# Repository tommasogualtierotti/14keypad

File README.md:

# 14keypad
14 keys programmable Macropad, based on RP2040 MCU from Raspberry Pi, running [KMK](https://github.com/KMKfw/kmk_firmware) firmware

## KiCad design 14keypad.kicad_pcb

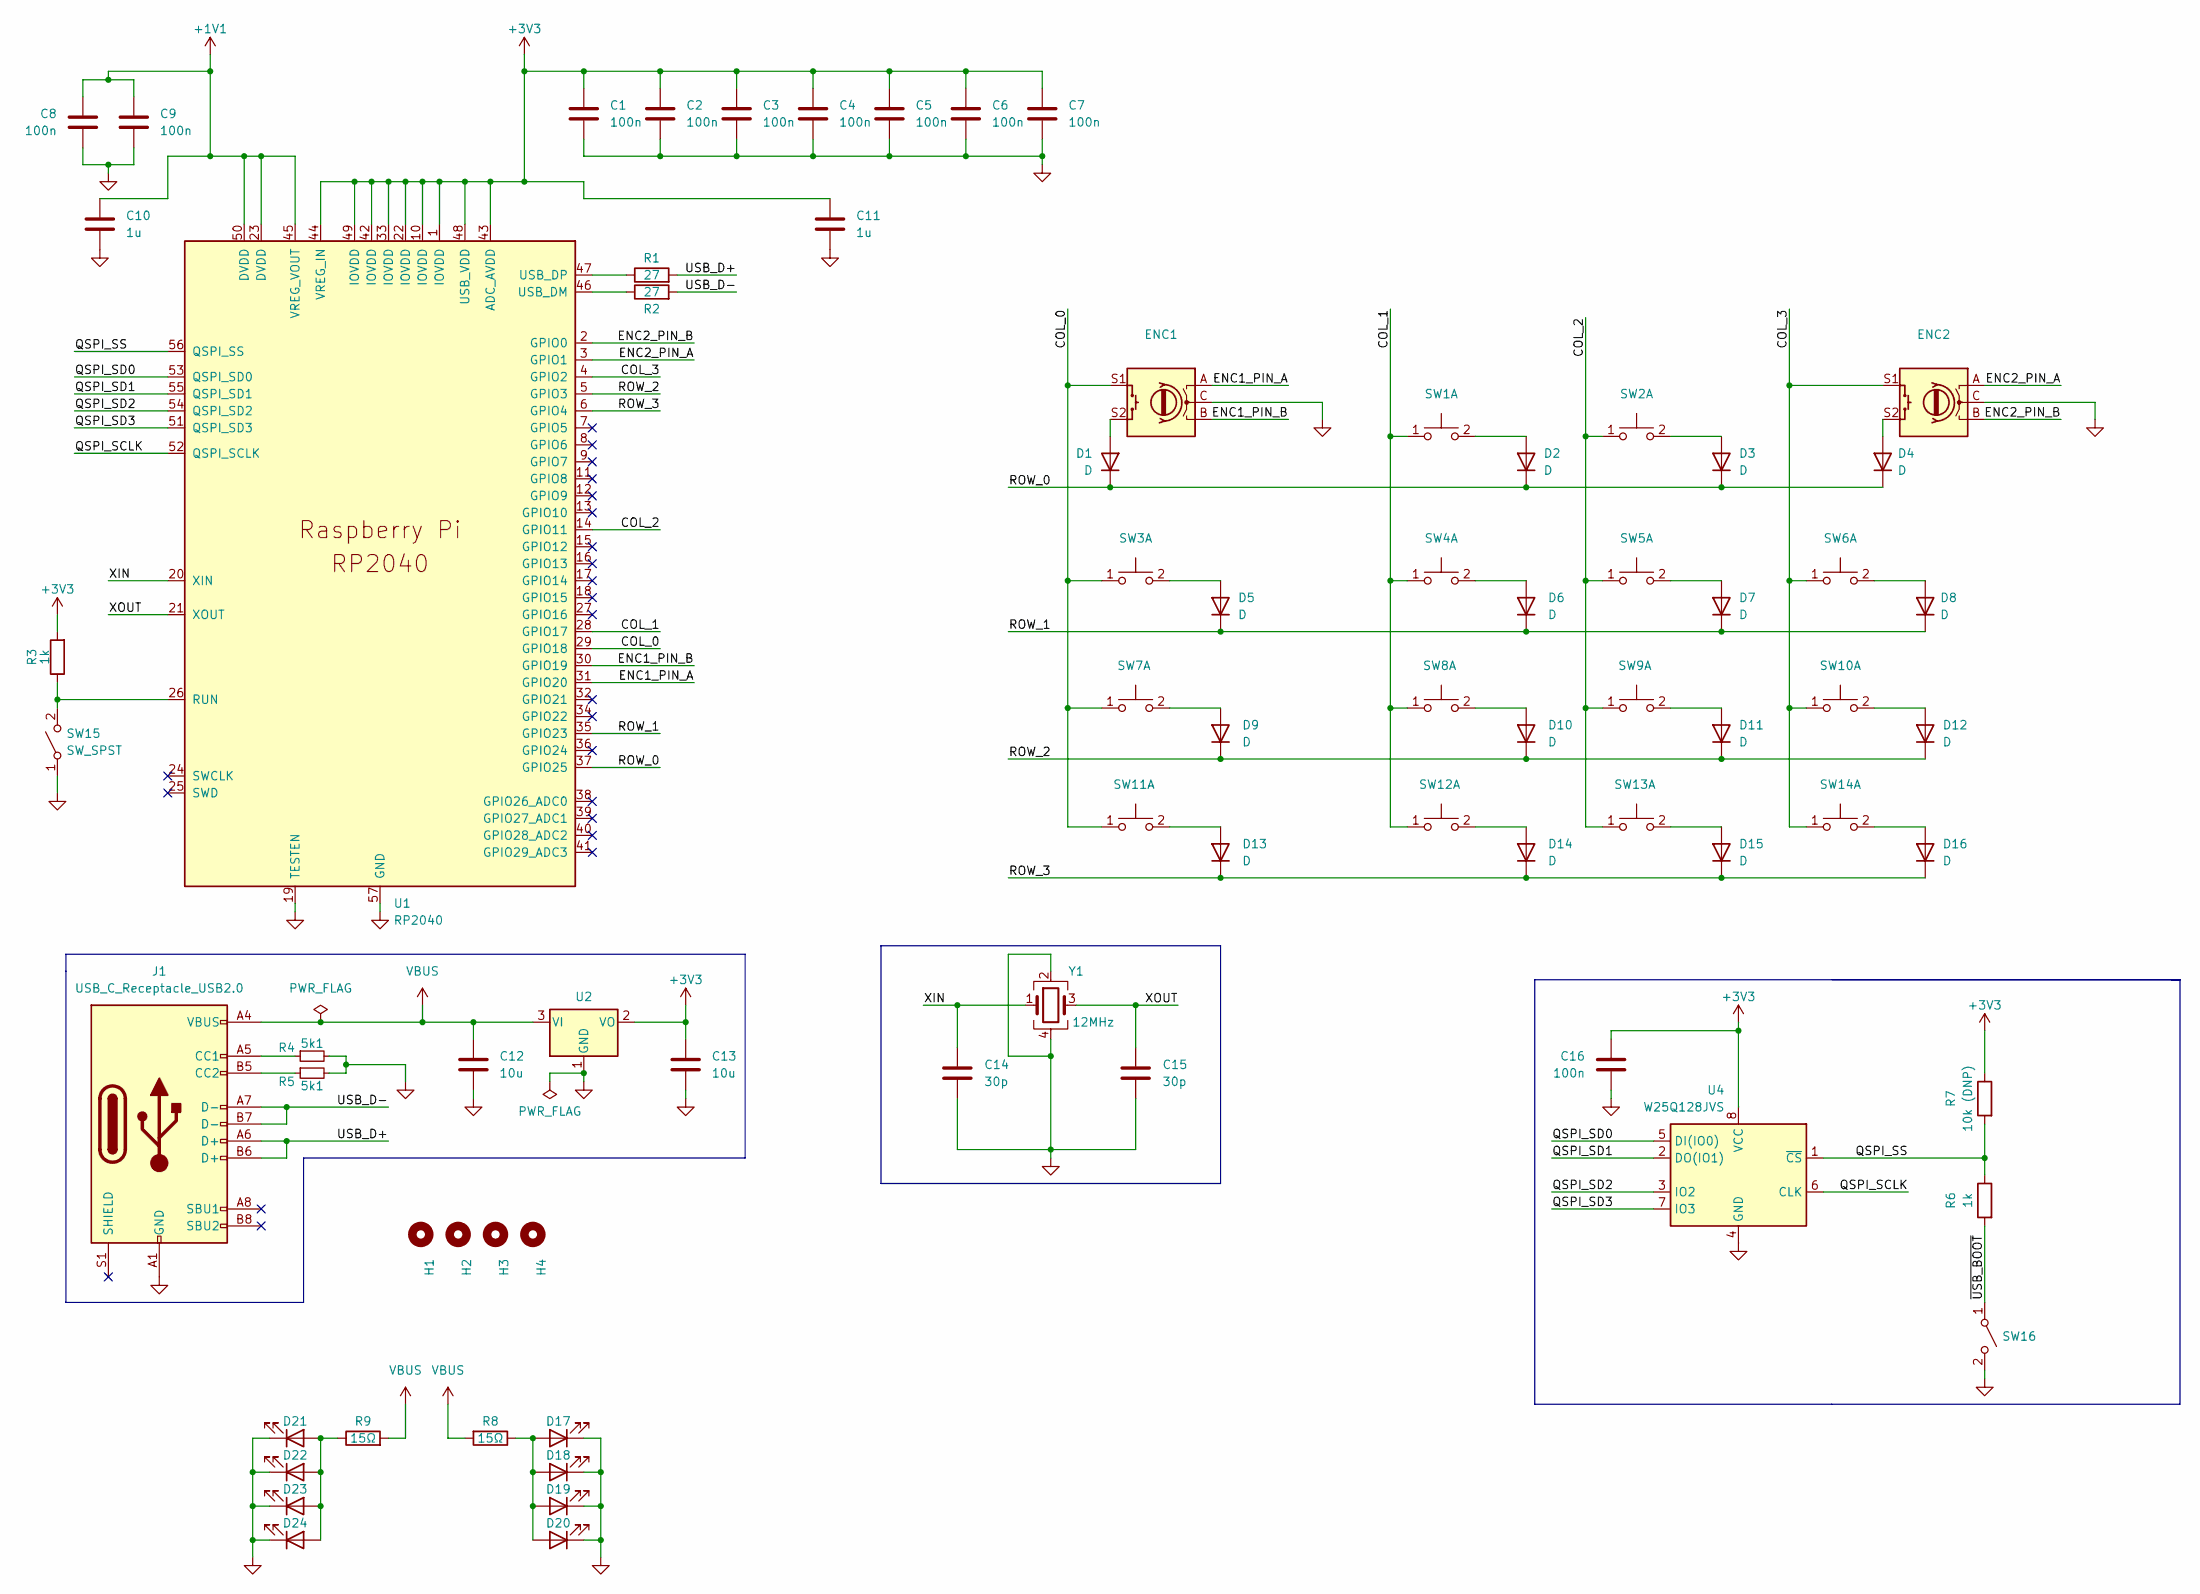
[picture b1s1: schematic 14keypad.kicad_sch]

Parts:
C1, C2, C3, C4, C5, C6, C7, C8, C9, C16: 100n; C_0402_1005Metric
C10, C11: 1u; C_0402_1005Metric
C12, C13: 10u; C_0603_1608Metric
C14, C15: 30p; C_0402_1005Metric
D1, D2, D3, D4, D5, D6, D7, D8, D9, D10, D11, D12, D13, D14, D15, D16: D; D_SOD-123
D17, D18, D19, D20, D21, D22, D23, D24: LED; D_0805_2012Metric
ENC1, ENC2: Encoder_Switch; RotaryEncoder_Alps_EC11E-Switch_Vertical_H20mm
H1, H2, H3, H4: MountingHole; MountingHole_2.2mm_M2
J1: USB_C_Receptacle_USB2.0; USB_C_Receptacle_XKB_U262-16XN-4BVC11
R1, R2: 27; R_0603_1608Metric
R3, R6: 1k; R_0402_1005Metric
R4, R5: 5k1; R_0402_1005Metric
R7: 10k (DNP); R_0402_1005Metric
R8: 15Ω; R_0805_2012Metric
R9: 15Ω; R_0805_2012Metric; JLCPCB_PART_NUMBER C17480
SW1, SW2, SW3, SW4, SW5, SW6, SW7, SW8, SW9, SW10, SW11, SW12, SW13, SW14: KEY_MX; SW_Cherry_MX_1.00u_PCB_UPDATED_FOOTPRINT_RIGHT_PIN_ASSIGNME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
SW15, SW16: SW_SPST; SW_Push_1P1T_XKB_TS-1187A
U1: RP2040; RP2040-QFN-56; JLCPCB_PART_NUMBER C2040
U2: NCP1117-3.3_SOT223; SOT-223-3_TabPin2
U4: W25Q128JVS; SOIC-8_5.23x5.23mm_P1.27mm
Y1: 12MHz; Crystal_SMD_3225-4Pin_3.2x2.5mm

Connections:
+1V1: C8.2, C9.1, C10.1, U1.23 (DVDD), U1.45 (VREG_VOUT), U1.50 (DVDD)
+3V3: C1.1, C2.1, C3.1, C4.1, C5.1, C6.1, C7.1, C11.1, C13.1, C16.1, R3.2, R7.1, U1.1 (IOVDD), U1.10 (IOVDD), U1.22 (IOVDD), U1.33 (IOVDD), U1.42 (IOVDD), U1.43 (ADC_AVDD), U1.44 (VREG_IN), U1.48 (USB_VDD), U1.49 (IOVDD), U2.2 (VO), U4.8 (VCC)
/COL_0: ENC1.S1, SW3.1, SW7.1, SW11.1, U1.29 (GPIO18)
/COL_1: SW1.1, SW4.1, SW8.1, SW12.1, U1.28 (GPIO17)
/COL_2: SW2.1, SW5.1, SW9.1, SW13.1, U1.14 (GPIO11)
/COL_3: ENC2.S1, SW6.1, SW10.1, SW14.1, U1.4 (GPIO2)
/ENC1_PIN_A: ENC1.A, U1.31 (GPIO20)
/ENC1_PIN_B: ENC1.B, U1.30 (GPIO19)
/ENC2_PIN_A: ENC2.A, U1.3 (GPIO1)
/ENC2_PIN_B: ENC2.B, U1.2 (GPIO0)
/QSPI_SCLK: U1.52 (QSPI_SCLK), U4.6 (CLK)
/QSPI_SD0: U1.53 (QSPI_SD0), U4.5 (DI(IO0))
/QSPI_SD1: U1.55 (QSPI_SD1), U4.2 (DO(IO1))
/QSPI_SD2: U1.54 (QSPI_SD2), U4.3 (IO2)
/QSPI_SD3: U1.51 (QSPI_SD3), U4.7 (IO3)
/QSPI_SS: R6.1, R7.2, U1.56 (QSPI_SS), U4.1 (~CS)
/ROW_0: D1.1 (K), D2.1 (K), D3.1 (K), D4.1 (K), U1.37 (GPIO25)
/ROW_1: D5.1 (K), D6.1 (K), D7.1 (K), D8.1 (K), U1.35 (GPIO23)
/ROW_2: D9.1 (K), D10.1 (K), D11.1 (K), D12.1 (K), U1.5 (GPIO3)
/ROW_3: D13.1 (K), D14.1 (K), D15.1 (K), D16.1 (K), U1.6 (GPIO4)
/USB_D+: J1.A6 (D+), J1.B6 (D+), R1.2
/USB_D-: J1.A7 (D-), J1.B7 (D-), R2.2
/XIN: C14.1, U1.20 (XIN), Y1.1
/XOUT: C15.1, U1.21 (XOUT), Y1.3
/~USB_BOOT: R6.2, SW16.1 (A)
GND: C1.2, C2.2, C3.2, C4.2, C5.2, C6.2, C7.2, C8.1, C9.2, C10.2, C11.2, C12.2, C13.2, C14.2, C15.2, C16.2, D17.1 (K), D18.1 (K), D19.1 (K), D20.1 (K), D21.1 (K), D22.1 (K), D23.1 (K), D24.1 (K), ENC1.C, ENC2.C, J1.A1 (GND), J1.A12 (GND), J1.B1 (GND), J1.B12 (GND), R4.2, R5.2, SW15.1 (A), SW16.2 (B), U1.19 (TESTEN), U1.57 (GND), U2.1 (GND), U4.4 (GND), Y1.2, Y1.4
unnamed: D1.2 (A), ENC1.S2
unnamed: D2.2 (A), SW1.2
unnamed: D3.2 (A), SW2.2
unnamed: D4.2 (A), ENC2.S2
unnamed: D5.2 (A), SW3.2
unnamed: D6.2 (A), SW4.2
unnamed: D7.2 (A), SW5.2
unnamed: D8.2 (A), SW6.2
unnamed: D9.2 (A), SW7.2
unnamed: D10.2 (A), SW8.2
unnamed: D11.2 (A), SW9.2
unnamed: D12.2 (A), SW10.2
unnamed: D13.2 (A), SW11.2
unnamed: D14.2 (A), SW12.2
unnamed: D15.2 (A), SW13.2
unnamed: D16.2 (A), SW14.2
unnamed: D17.2 (A), D18.2 (A), D19.2 (A), D20.2 (A), R8.1
unnamed: D21.2 (A), D22.2 (A), D23.2 (A), D24.2 (A), R9.1
unnamed: J1.A5 (CC1), R4.1
unnamed: J1.B5 (CC2), R5.1
unnamed: R3.1, SW15.2 (B), U1.26 (RUN)
unnamed: R2.1, U1.46 (USB_DM)
unnamed: R1.1, U1.47 (USB_DP)
VBUS: C12.1, J1.A4 (VBUS), J1.A9 (VBUS), J1.B4 (VBUS), J1.B9 (VBUS), R8.2, R9.2, U2.3 (VI)

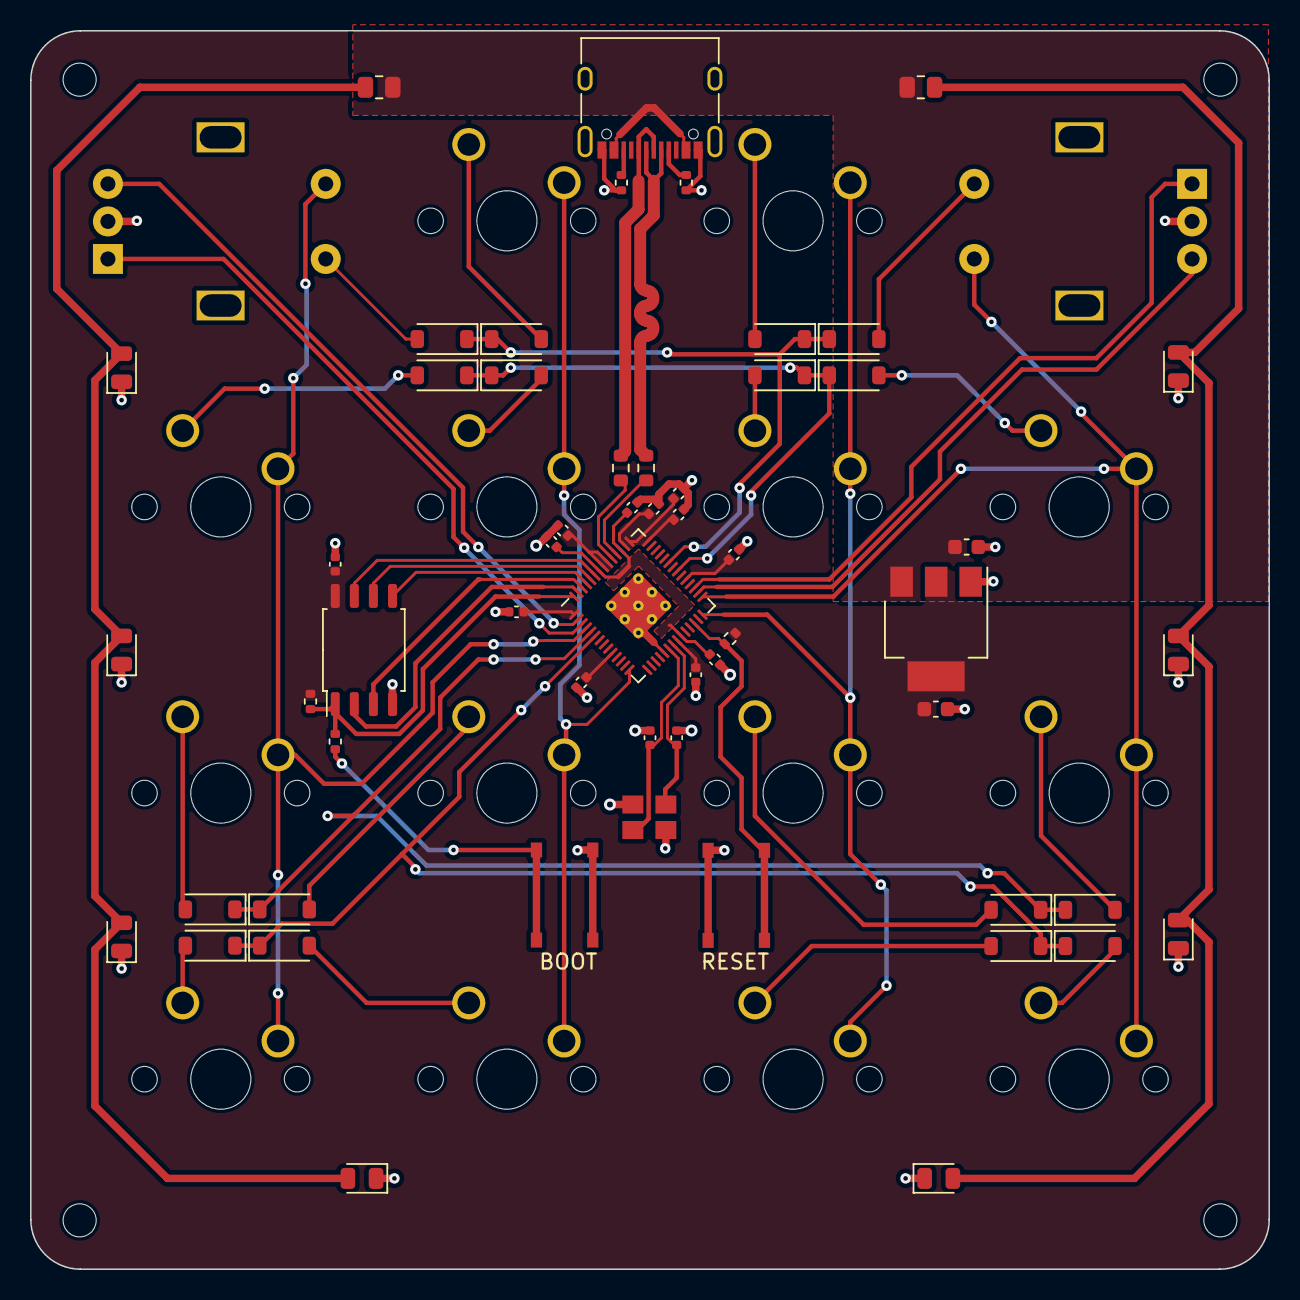
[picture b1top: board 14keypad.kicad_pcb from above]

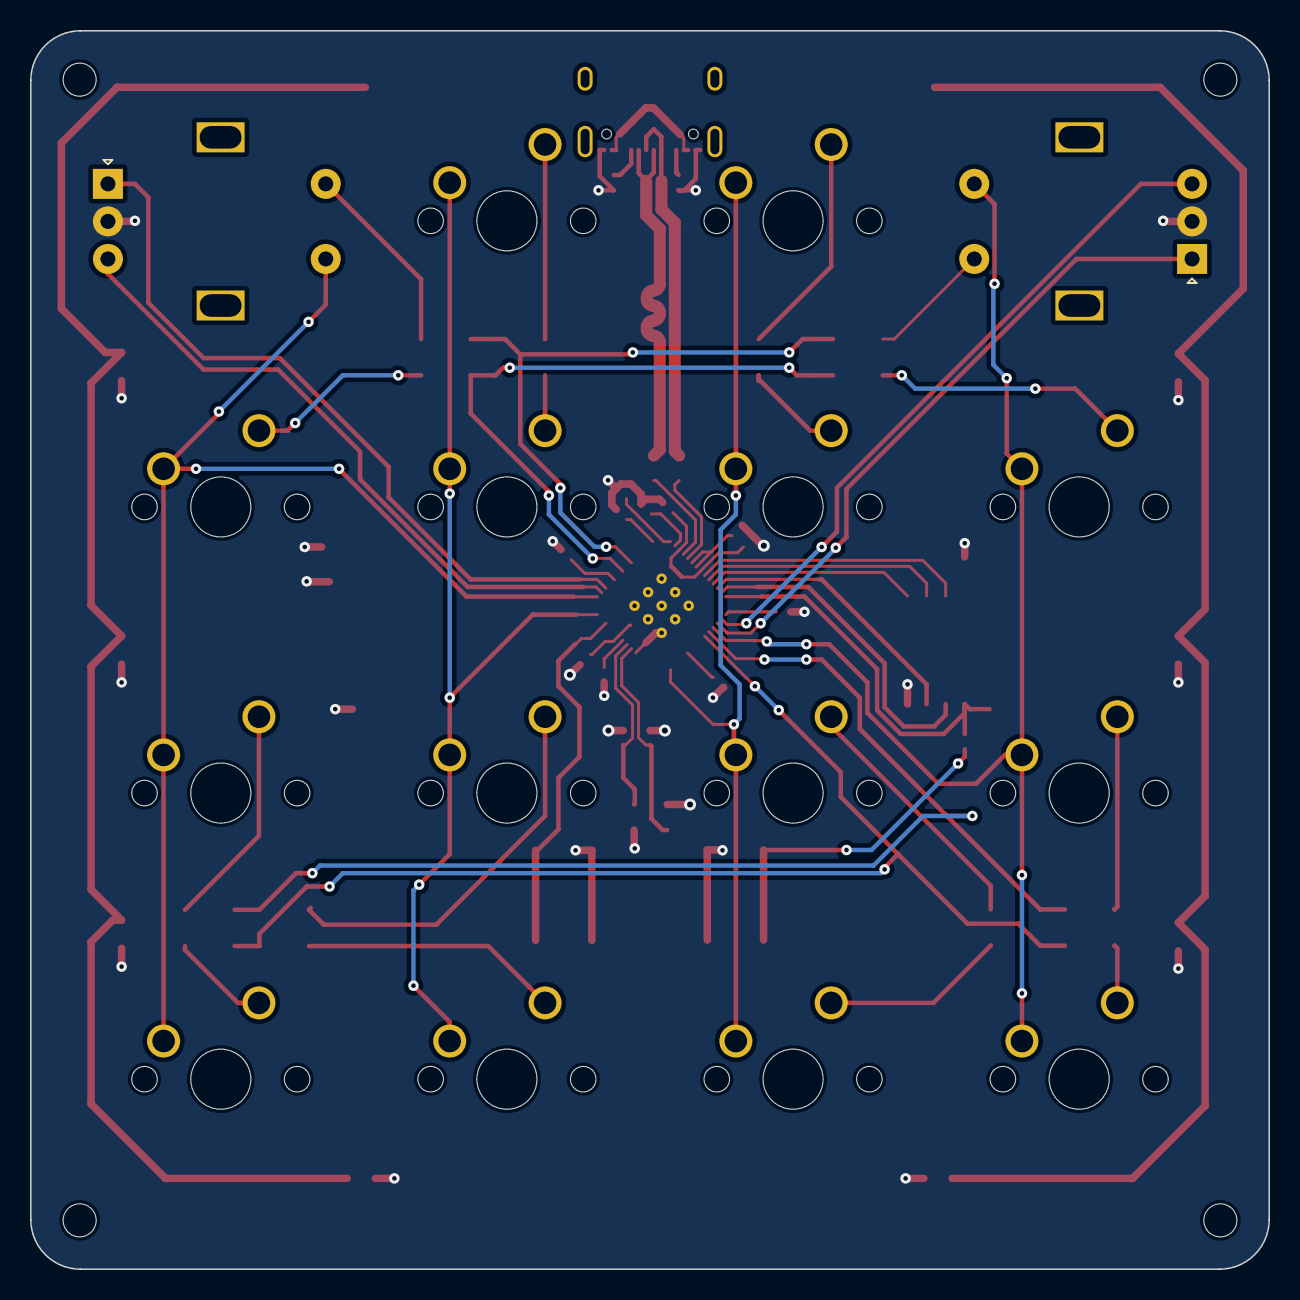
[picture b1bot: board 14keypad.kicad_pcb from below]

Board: 2 copper layers, 82.5 x 82.5 mm, 76 parts (16 on the bottom side), 50 nets.

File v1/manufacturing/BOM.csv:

"Item","Qty","Reference(s)","Value","LibPart","Footprint","Datasheet","DNP","LCSC Part #"
"1","10","C1, C2, C3, C4, C5, C6, C7, C8, C9, C16","100n","Device:C","Capacitor_SMD:C_0402_1005Metric","~","","C1525"
"2","2","C10, C11","1u","Device:C","Capacitor_SMD:C_0402_1005Metric","~","","C52923"
"3","2","C12, C13","10u","Device:C","Capacitor_SMD:C_0603_1608Metric","~","","C19702"
"4","2","C14, C15","30p","Device:C","Capacitor_SMD:C_0402_1005Metric","~","","C1570"
"5","16","D1, D2, D3, D4, D5, D6, D7, D8, D9, D10, D11, D12, D13, D14, D15, D16, ","D",":D_5","Diode_SMD:D_SOD-123","~","","C81598"
"23","1","J1","USB_C_Receptacle_USB2.0","Connector:USB_C_Receptacle_USB2.0","Connector_USB:USB_C_Receptacle_XKB_U262-16XN-4BVC11","~","","C319148"
"24","2","R1, R2","27","Device:R","Resistor_SMD:R_0603_1608Metric","~","","C25190"
"25","1","R3, R7","10k","Device:R","Resistor_SMD:R_0402_1005Metric","~","","C25744"
"26","2","R4, R5","5k1","Device:R_Small","Resistor_SMD:R_0402_1005Metric","~","","C25905"
"27","1","R6","1k","Device:R","Resistor_SMD:R_0402_1005Metric","~","","C11702"
"29","2","SW15, SW16","SW_SPST","Switch:SW_SPST","Button_Switch_SMD:SW_Push_1P1T_XKB_TS-1187A","~","C318884"
"30","1","U1","RP2040",":RP2040_1","RP2040_minimal:RP2040-QFN-56","","","C2040"
"31","1","U2","AMS1117-3.3_SOT223","Regulator_Linear:AMS1117-3.3_SOT223","Package_TO_SOT_SMD:SOT-223-3_TabPin2","~","","C6186"
"32","1","U4","W25Q128JVS","Memory_Flash:W25Q128JVS","Package_SO:SOIC-8_5.23x5.23mm_P1.27mm","http://www.winbond.com/resource-files/w25q128jv_dtr%20revc%2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","","C97521"
"34","1","Y1","12MHz","Device:Crystal_GND24","Crystal:Crystal_SMD_3225-4Pin_3.2x2.5mm","~","","C9002"

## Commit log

2023-10-14 general commit
2023-10-14 add assembled macropad photo
2023-10-15 add assembled photo
2025-06-05 add gerbers file for manufacturing
